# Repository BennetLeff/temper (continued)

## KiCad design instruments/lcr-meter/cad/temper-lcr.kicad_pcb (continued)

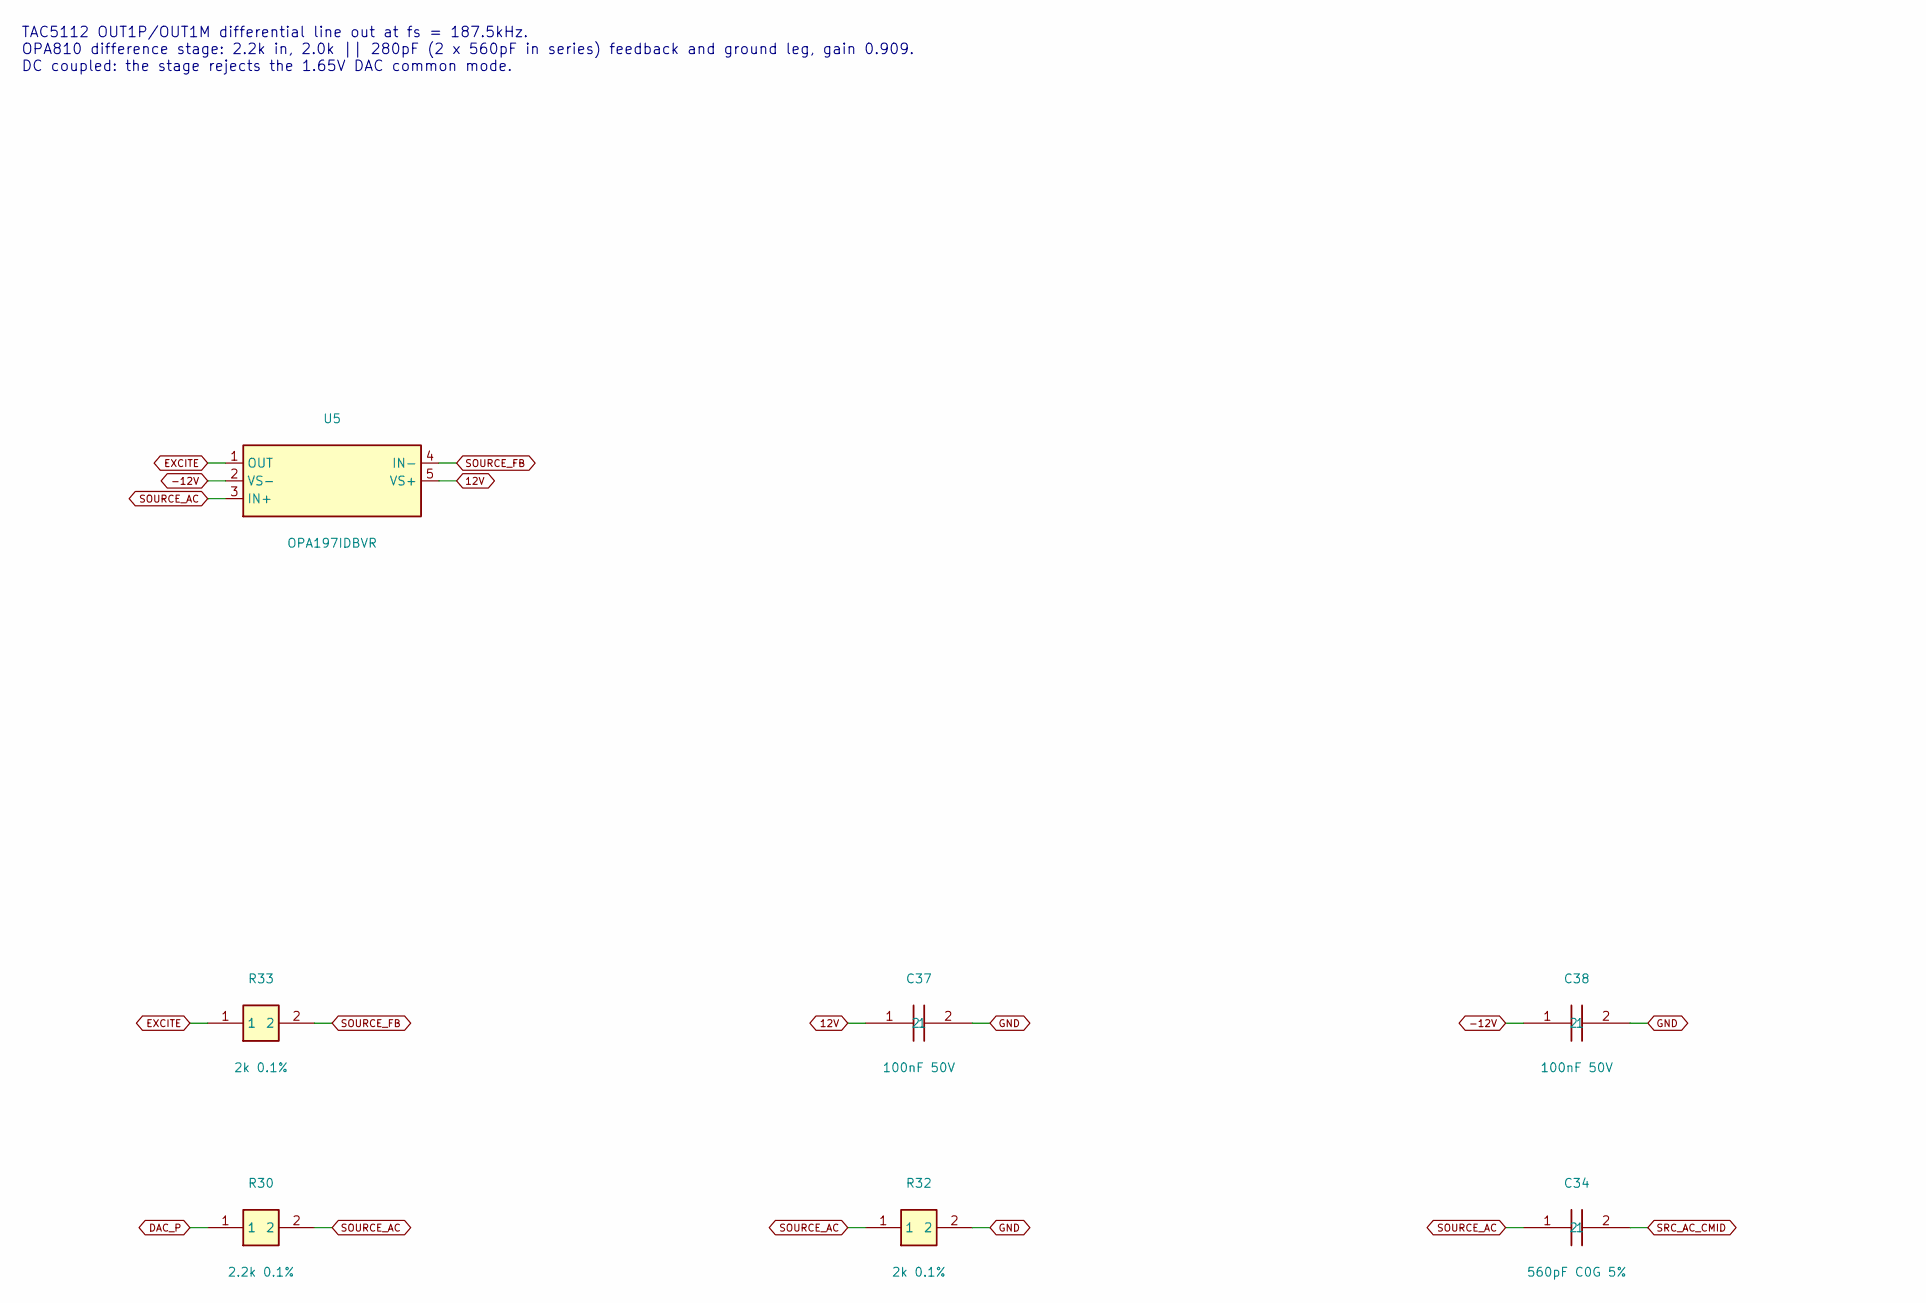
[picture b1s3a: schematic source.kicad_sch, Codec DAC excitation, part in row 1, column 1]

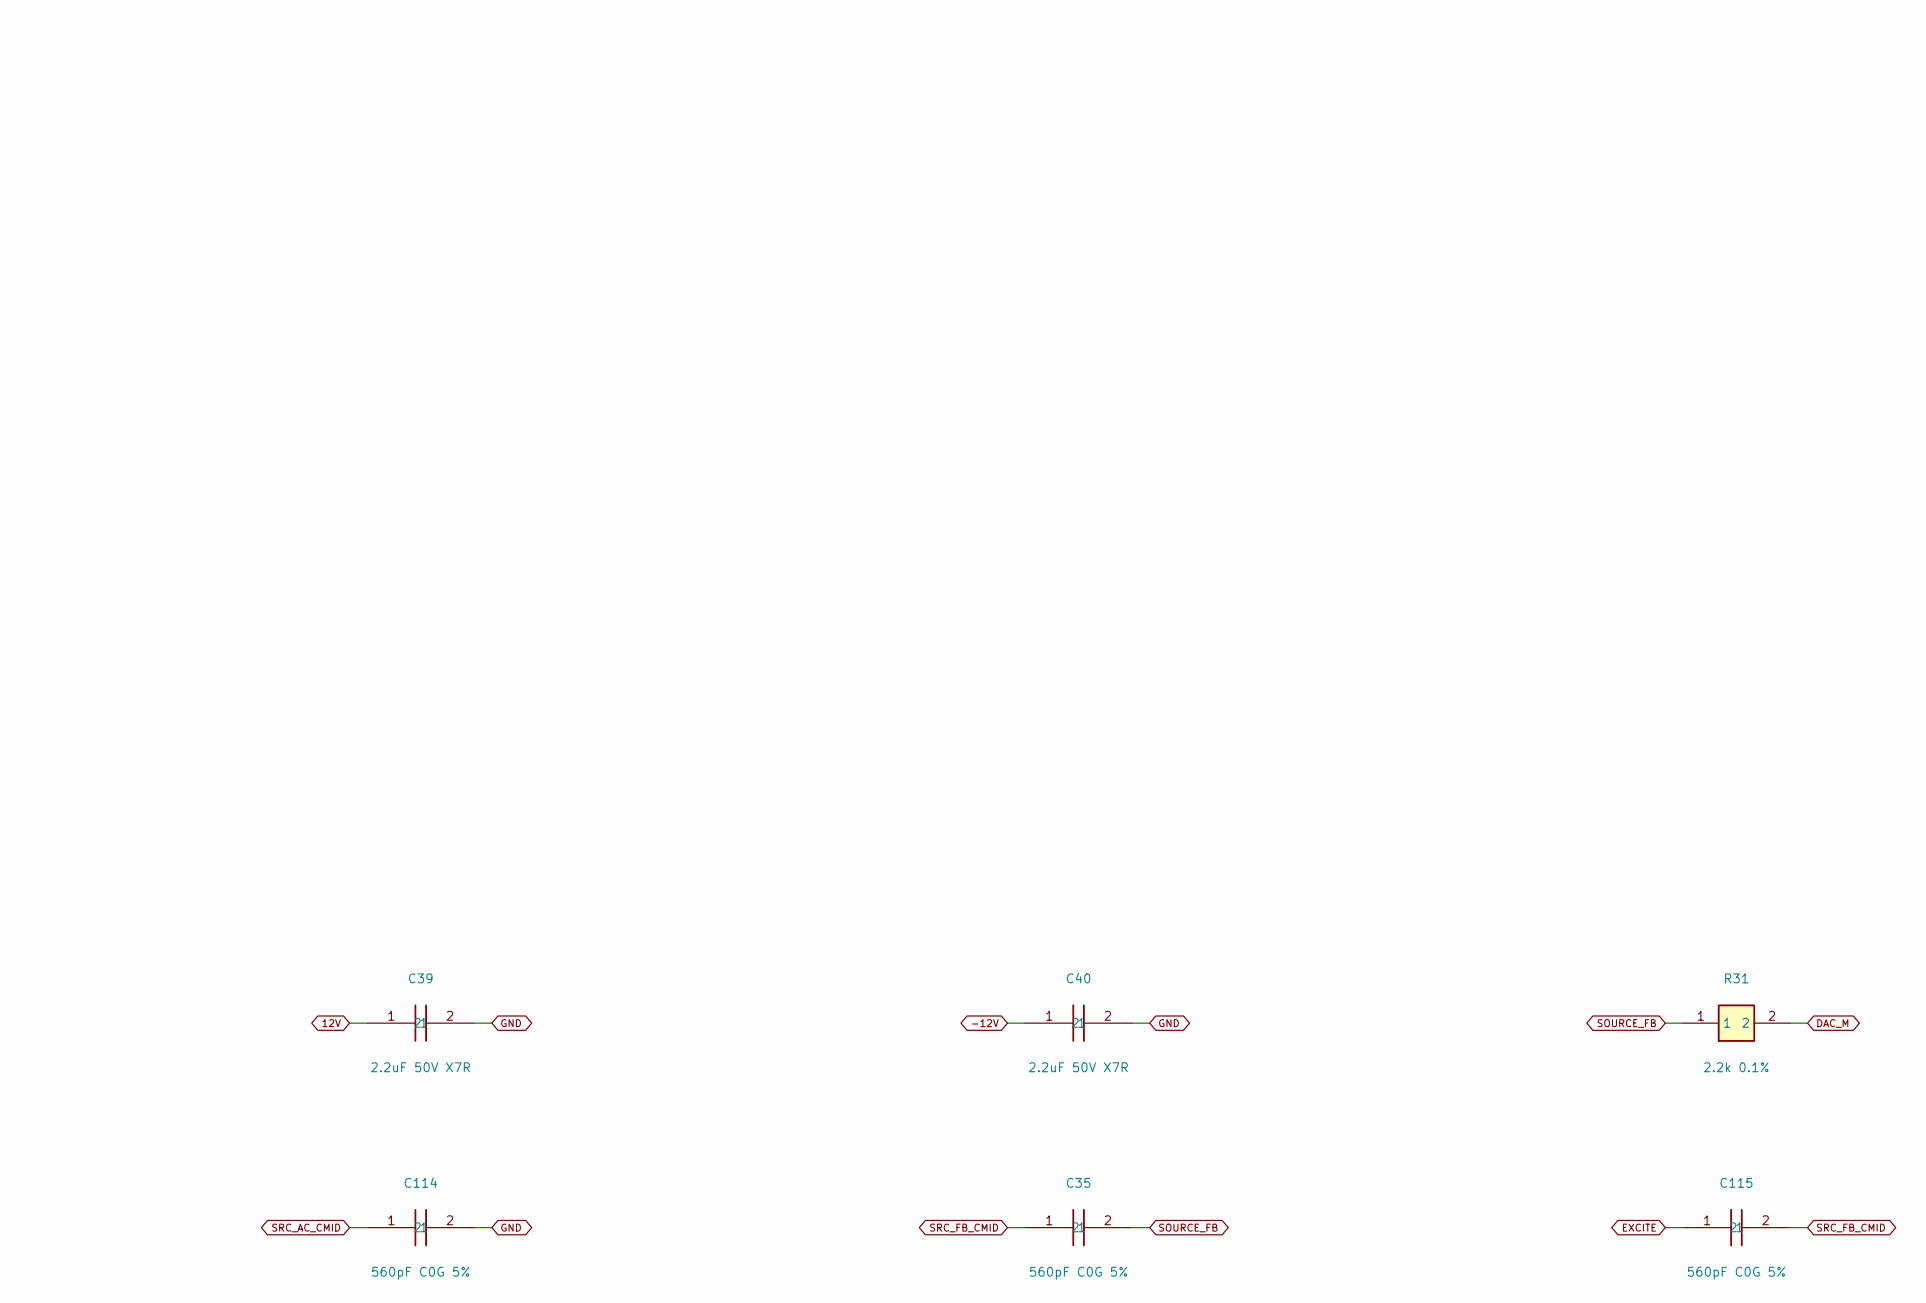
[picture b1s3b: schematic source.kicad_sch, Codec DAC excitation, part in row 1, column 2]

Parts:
C34, C35, C114, C115: 560pF C0G 5%; C_0603_1608Metric; MPN CC0603JRNPO9BN561; LCSC C107054
C37, C38: 100nF 50V; C_0603_1608Metric; MPN CC0603KRX7R9BB104; LCSC C14663
C39, C40: 2.2uF 50V X7R; C_0805_2012Metric; MPN CC0805KKX7R9BB225; LCSC C125847
R30, R31: 2.2k 0.1%; R_0603_1608Metric; MPN RT0603BRD072K2L; LCSC C861295
R32, R33: 2k 0.1%; R_0603_1608Metric; MPN AR03BTCX2001; LCSC C318130
U5: OPA197IDBVR; SOT-23-5; MPN OPA197IDBVR; LCSC C221351

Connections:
12V: C37.1, C39.1, U5.5 (VS+); also elsewhere on the board
-12V: C38.1, C40.1, U5.2 (VS-); also elsewhere on the board
DAC_M: R31.2; also elsewhere on the board
DAC_P: R30.1; also elsewhere on the board
EXCITE: C115.1, R33.1, U5.1 (OUT); also elsewhere on the board
GND: C37.2, C38.2, C39.2, C40.2, C114.2, R32.2; also elsewhere on the board
SOURCE_AC: C34.1, R30.2, R32.1, U5.3 (IN+)
SOURCE_FB: C35.2, R31.1, R33.2, U5.4 (IN-)
SRC_AC_CMID: C34.2, C114.1
SRC_FB_CMID: C35.1, C115.2

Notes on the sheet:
TAC5112 OUT1P/OUT1M differential line out at fs = 187.5kHz. OPA810 difference stage: 2.2k in, 2.0k || 280pF (2 x 560pF in series) feedback and ground leg, gain 0.909. DC coupled: the stage rejects the 1.65V DAC common mode.

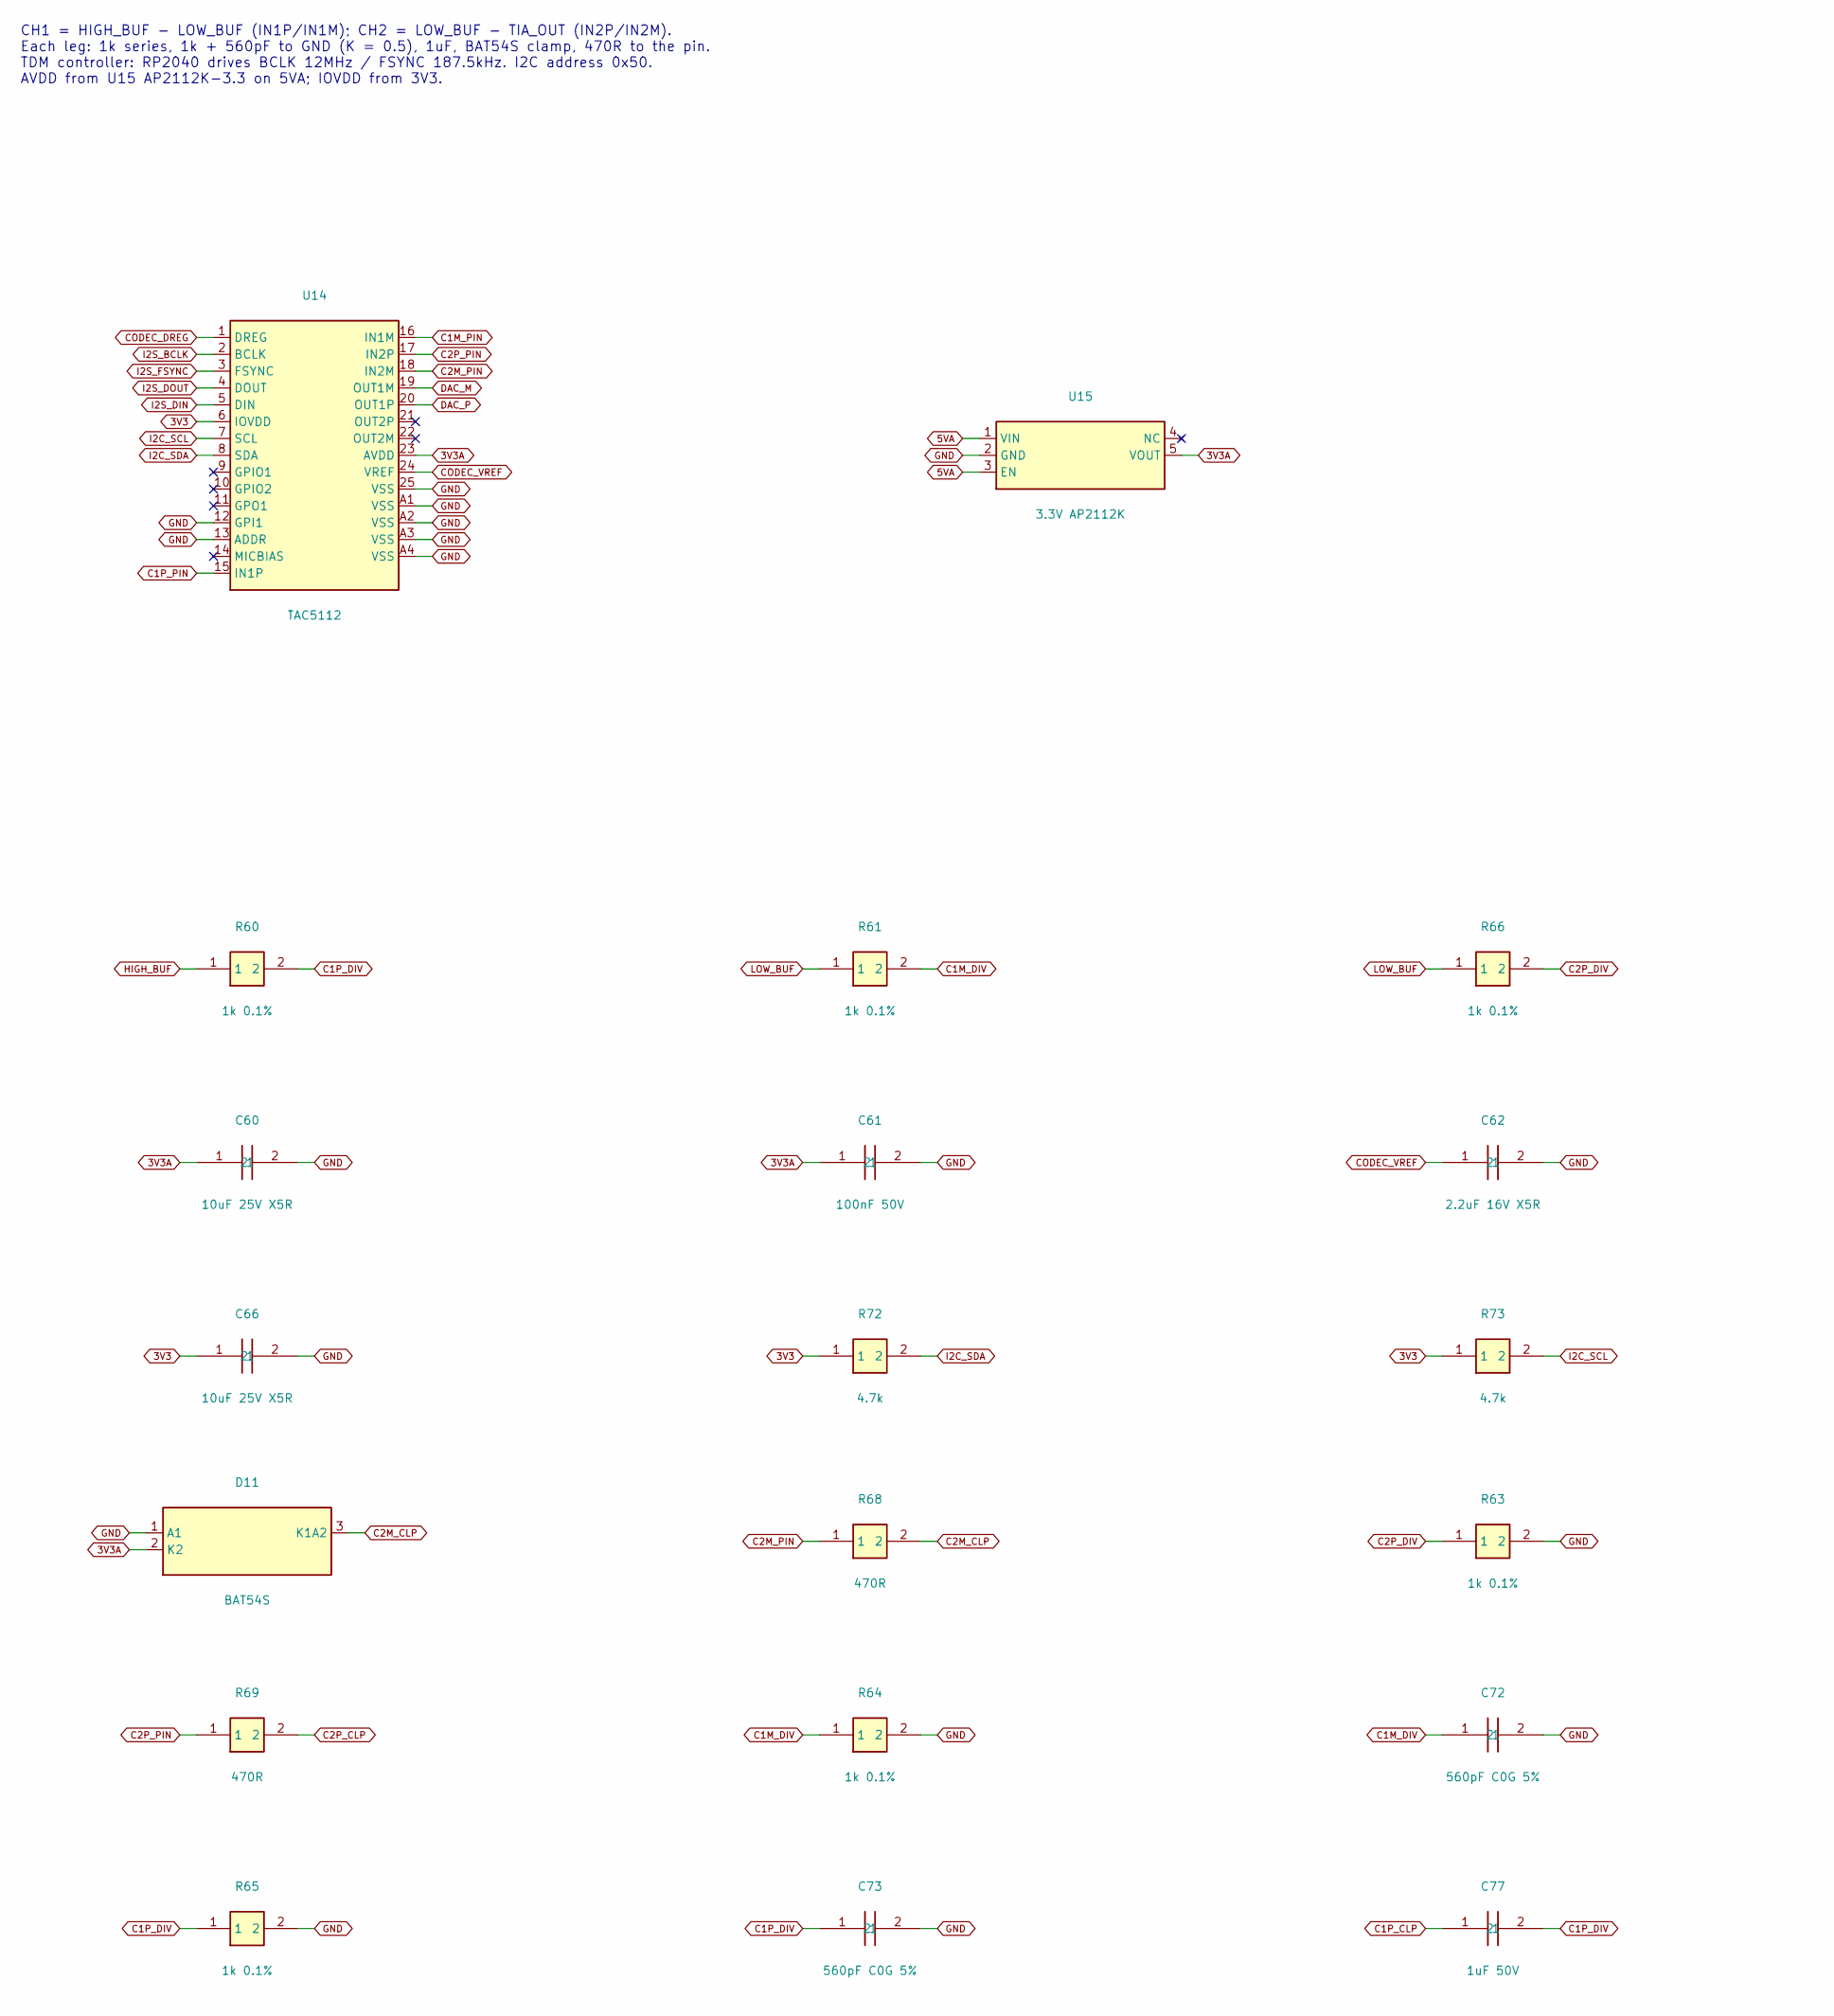
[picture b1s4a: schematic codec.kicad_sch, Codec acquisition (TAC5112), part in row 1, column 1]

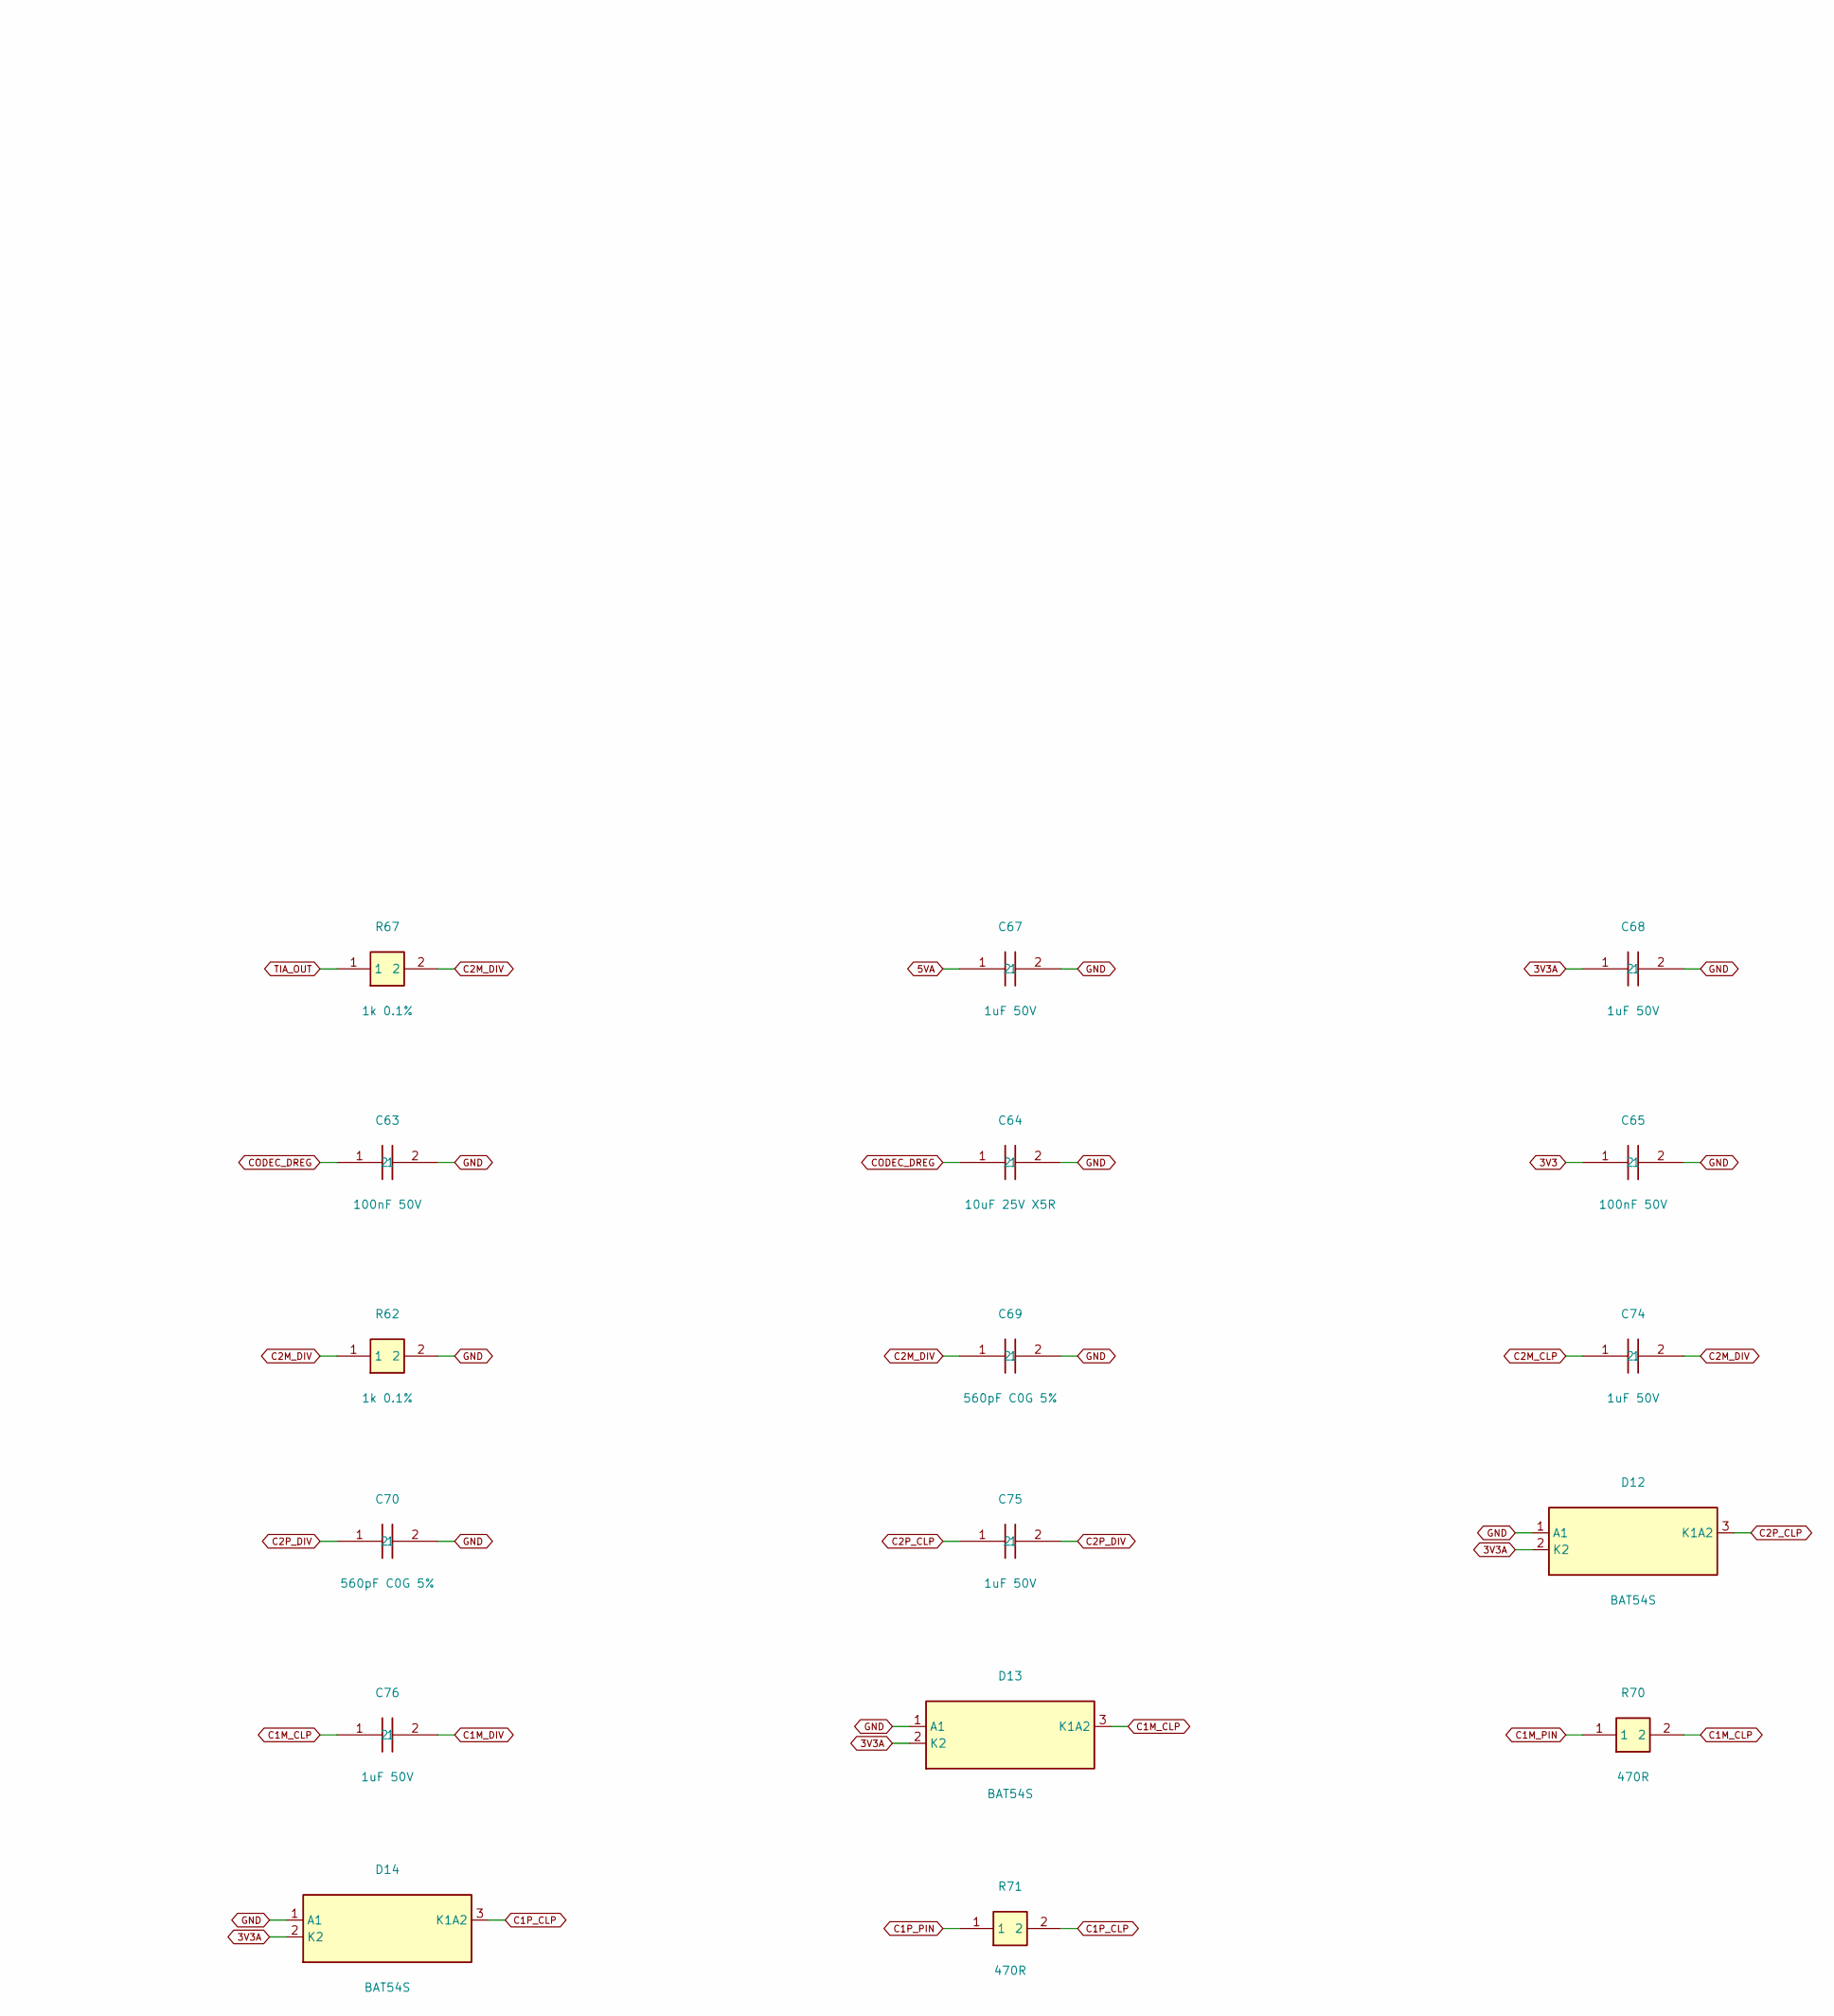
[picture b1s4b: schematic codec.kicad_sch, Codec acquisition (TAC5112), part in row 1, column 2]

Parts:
C60, C64, C66: 10uF 25V X5R; C_0805_2012Metric; MPN CL21A106KAYNNNE; LCSC C15850
C61, C63, C65: 100nF 50V; C_0603_1608Metric; MPN CC0603KRX7R9BB104; LCSC C14663
C62: 2.2uF 16V X5R; C_0603_1608Metric; MPN CL10A225KO8NNNC; LCSC C23630
C67, C68, C74, C75, C76, C77: 1uF 50V; C_0805_2012Metric; MPN CL21B105KBFNNNE; LCSC C28323
C69, C70, C72, C73: 560pF C0G 5%; C_0603_1608Metric; MPN CC0603JRNPO9BN561; LCSC C107054
D11, D12, D13, D14: BAT54S; SOT-23; MPN BAT54S; LCSC C7420333
R60, R61, R62, R63, R64, R65, R66, R67: 1k 0.1%; R_0603_1608Metric; MPN RT0603BRD071KL; LCSC C110776
R68, R69, R70, R71: 470R; R_0603_1608Metric; MPN 0603WAF4700T5E; LCSC C23179
R72, R73: 4.7k; R_0603_1608Metric; MPN 0603WAF4701T5E; LCSC C23162
U14: TAC5112; TI_RGE0024R_VQFN-24-1EP_4x4mm_P0.5mm_EP2.1mm_CornerPads; MPN TAC5112IRGER; LCSC C44853692
U15: 3.3V AP2112K; SOT-23-5; MPN AP2112K-3.3TRG1; LCSC C51118

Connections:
3V3: C65.1, C66.1, R72.1, R73.1, U14.6 (IOVDD); also elsewhere on the board
3V3A: C60.1, C61.1, C68.1, D11.2 (K2), D12.2 (K2), D13.2 (K2), D14.2 (K2), U14.23 (AVDD), U15.5 (VOUT)
5VA: C67.1, U15.1 (VIN), U15.3 (EN); also elsewhere on the board
C1M_CLP: C76.1, D13.3 (K1A2), R70.2
C1M_DIV: C72.1, C76.2, R61.2, R64.1
C1M_PIN: R70.1, U14.16 (IN1M)
C1P_CLP: C77.1, D14.3 (K1A2), R71.2
C1P_DIV: C73.1, C77.2, R60.2, R65.1
C1P_PIN: R71.1, U14.15 (IN1P)
C2M_CLP: C74.1, D11.3 (K1A2), R68.2
C2M_DIV: C69.1, C74.2, R62.1, R67.2
C2M_PIN: R68.1, U14.18 (IN2M)
C2P_CLP: C75.1, D12.3 (K1A2), R69.2
C2P_DIV: C70.1, C75.2, R63.1, R66.2
C2P_PIN: R69.1, U14.17 (IN2P)
CODEC_DREG: C63.1, C64.1, U14.1 (DREG)
CODEC_VREF: C62.1, U14.24 (VREF)
DAC_M: U14.19 (OUT1M); also elsewhere on the board
DAC_P: U14.20 (OUT1P); also elsewhere on the board
GND: C60.2, C61.2, C62.2, C63.2, C64.2, C65.2, C66.2, C67.2, C68.2, C69.2, C70.2, C72.2, C73.2, D11.1 (A1), D12.1 (A1), D13.1 (A1), D14.1 (A1), R62.2, R63.2, R64.2, R65.2, U14.12 (GPI1), U14.13 (ADDR), U14.25 (VSS), U14.A1 (VSS), U14.A2 (VSS), U14.A3 (VSS), U14.A4 (VSS), U15.2 (GND); also elsewhere on the board
HIGH_BUF: R60.1; also elsewhere on the board
I2C_SCL: R73.2, U14.7 (SCL); also elsewhere on the board
I2C_SDA: R72.2, U14.8 (SDA); also elsewhere on the board
I2S_BCLK: U14.2 (BCLK); also elsewhere on the board
I2S_DIN: U14.5 (DIN); also elsewhere on the board
I2S_DOUT: U14.4 (DOUT); also elsewhere on the board
I2S_FSYNC: U14.3 (FSYNC); also elsewhere on the board
LOW_BUF: R61.1, R66.1; also elsewhere on the board
TIA_OUT: R67.1; also elsewhere on the board

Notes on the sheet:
CH1 = HIGH_BUF - LOW_BUF (IN1P/IN1M); CH2 = LOW_BUF - TIA_OUT (IN2P/IN2M). Each leg: 1k series, 1k + 560pF to GND (K = 0.5), 1uF, BAT54S clamp, 470R to the pin. TDM controller: RP2040 drives BCLK 12MHz / FSYNC 187.5kHz. I2C address 0x50. AVDD from U15 AP2112K-3.3 on 5VA; IOVDD from 3V3.
